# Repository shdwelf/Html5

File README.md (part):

# bip39-haiku-workbench

Offline workbench for mining **BIP-39 mnemonics that scan as 5-7-5 haiku**, deriving
their BIP-44 addresses, and moving data between tools through a **piped inbox**.

The application now combines both repository lineages. The canonical main canvas is
the complete uploaded **23 August Gen2 Webxdc/quine build**, with a surgical Poetry
validator repair applied before it executes rather than replacement look-alike
components. The small `⌘` switcher opens the maintained TypeScript recovery suite
and every other distinct, non-empty HTML application from the gen-2 patch.

```bash
npm install
npm run dev     # http://localhost:5173
npm test        # full test suite, including byte-identity locks for the uploads
npm run build   # dist/index.html + dist/bip39-haiku-workbench.xdc
```

The production build is inlined by `vite-plugin-singlefile`, so `dist/index.html`
runs standalone from the filesystem. `scripts/build-xdc.mjs` then packages that
same combined application, its icon, manifest, and static companion tools as a
Webxdc ZIP for ArcaneChat / Delta Chat.

## Combined codebases

| Switcher entry | Source | Integration rule |
| --- | --- | --- |
| **Gen2 · Aug 23** (default) | `bip39-haiku-workbench-gen2-2026-08-23T11-46-10-756Z.html` | Full uploaded 12-tool canvas plus strict Poetry syllable repair |
| **Gen2 · Aug 14** | `bip39-haiku-workbench-gen2-2026-08-14T20-01-22-058Z.html` | Exact earlier seven-tool generation |
| **Quip build** | `bip39-haiku-workbench-quip.html` | Exact mnemonic explorer bundle |
| **Classic wallet** | `bip39_haiku_wallet.html` | Exact standalone miner and encrypted wallet list |
| **Pattern validator** | `haikubip39.html` | Exact classic haiku/repeated-word validator |
| **Recovery suite** | `src/` | Maintained React/TypeScript tools described below |

The applications run in same-origin `iframe srcdoc` boundaries because every upload
is already a complete compiled document with its own React runtime, global CSS,
`#root`, storage, and download handlers. This is deliberate isolation, not a visual
port: `test/codebase-archive.test.tsx` pins the original SHA-256 of all five documents,
and `test/poetry-validation.test.ts` signature-locks the two targeted Gen2 repairs.
The old Poetry counter double-subtracted consonant-`le` endings, while its line builder
could abandon a target after drawing a word that did not fit. The repair shares the
validator pronunciation table, only selects words that fit the remainder, and accepts
exact form counts—never a third line of 4 or 6 for 5-7-5. The second 23 August upload
is omitted only because it has the same SHA-256 as the first; `bip39haiku.html` is
omitted because it is zero bytes.

## Provenance

This repository was empty apart from a README. The application source was recovered
from the archive repo [`shdwelf/Html5-sync-incoming`](https://github.com/shdwelf/Html5-sync-incoming):

| Piece | Recovered from |
| --- | --- |
| Workbench app (React + Vite + Tailwind, `src/lib/wallet.ts`, `src/lib/syllables.ts`, `src/lib/enso.ts`) | `build-bip-39-haiku-wallet.zip` |
| Piped inbox concept and UI | `hyper-portal-2.27.0-PIPED-installer.html` (inside `Internal storage.7z`) |
| Recovery Lab (missing-word brute force, typo/anagram repair, vanity mining) | `crypto-mnemonic-mining-app.zip` |
| Art Gallery catalog, greedy 5-7-5 fallback, syllable-exception cleanup | vanilla workbench in [`shdwelf/Html5`](https://github.com/shdwelf/Html5) (`js/haiku-catalog.js`, `js/syllables.js`) |
| Vault file format + standalone decryptor | `HAIKUv4/v5`/`DECRYPTORv1.html` lineage (`Haiku Supplies.zip`) and the vanilla workbench's WebCrypto vault |

The two never shipped together: the haiku workbench had no inbox, and the
hyper-portal build that had the inbox had no haiku tool. Wiring them together —
and repairing the inbox on the way — is what this repo does.

`scripts/wormhole-fetch.mjs` is a small utility kept from that recovery work:
given `WH_URL=<link>` it opens a wormhole.app drop in real chromium (via
playwright) and captures every file — the link is end-to-end encrypted in the
URL fragment, so only a real browser can decrypt it. It runs anywhere
playwright + chromium are installed (a laptop, a GitHub runner with the
workflow permission).

## Repository-wide Java / TiddlyWiki editions

The new [Repository Wiki build](tools/wiki-workspace/README.md) produces actual
ACME/TJWS-hosted `wiki.in.a.jar`, `more.wiki.in.a.jar`, and `tiddlywiki.in.a.jar`,
plus a native TiddlyWiki HTML/Webxdc edition and MediaWiki XML export. Each JAR
contains a per-file source catalog and a deduplicated exact-byte repository vault,
with private caches/credential paths explicitly excluded. The extended library
adds backlinks, bibliographic URLs, revision conflicts/history and Haiku-v1
compatible encrypted page/file exchange. These are **new repository editions**,
not a claim to have recovered historical More Wiki 0.9.9 or translated arbitrary
JavaScript into JavaCard. See the [source-checked research and limitations](docs/wiki-workspace-research-2026-10-15.md).

```sh
npm ci
npm run build:wiki-workspace           # JDK 11+, Python 3, tar, curl; outputs dist/wiki/
java -jar dist/wiki/more.wiki.in.a.jar 3003
npm run test:wiki-workspace
npm run test:wiki-server               # real executable-JAR HTTP + persistence tests
```

The classic wiki's Calendar now uses font-independent SVG navigation, an
always-visible month grid and an event-page form; no pre-existing events are
required. TiddlyWiki HTML/XDC carry previews and metadata; the complete eligible
binary vault lives in the JAR editions. Nothing is uploaded to a remote wiki.

## Standalone viewers

- **[HTML5 Offline Viewer](offline-viewer.html)** — curated public catalogue for the locally bundled Helios Observatory and Prime Viewer apps, plus the local WebXDC player. `python3 scripts/build-private-html5-offline-viewer.py` creates a separate ignored delivery ZIP from the same fixed app allowlist.
- **[HTML5 Offline Library for Android](apps/html5-offline-launcher/README.md)** — public and curated private APK build instructions. CI publishes only the public APK artifact; the two-app private APK is built and verified without public artifact upload.
- **[Wiki in a Jar](wikiinajar.html)** — the 2008 USB-stick personal wiki (`wiki.in.a.jar` 0.8) rebuilt as one offline HTML file and a Webxdc bundle: same `.wiki` page model, same `[[wiki:]]`/`[[img:]]`/`[[djvu:]]`/`[[tags:]]` namespaces, vCard contacts, DjVu reading via the vendored WASM decoder, and webxdc chat sync. Ships as `wikiinajar.xdc` (`npm run build:wikiinajar`) with the repository Markdown library (root deep dives + `docs/*.md`) converted to wiki pages in its Docs tab; see [the deep dive](wikiinajar-deep-dive.md), the seeded **Wiki in a Jar** documentation page inside the app, and the Java-side patch in [tools/wikiinajar/](tools/wikiinajar/).
- **[Keyspace Viewer](keyspace.html)** — BIP-39 geometry, measured statistical layers, wallet derivatives, and keyspace projections.
- **[Prime Viewer](prime.html)** — exact prime atlas, residue-class solar system, prime constellations, counting statistics, gaps, and integer inspection. See [PRIME.md](PRIME.md).
- **[Helios Observatory](astronomy.html)** — time-propagated solar orrery, curated celestial catalog, Earth-centered NEO radar, and modeled meteor streams. See [ASTRONOMY.md](ASTRONOMY.md).
- **[Flash Decompiler Timeline](flash-decompiler.html)** — Wayback/NATA2-style raw SWF retrieval, configurable CORS proxy triage, Behind The Dune version timeline, easter-egg notes, and a GitHub Actions path for JPEXS/FFDec decompilation without committing large NSFW binaries.
- **[Red October · 4D Command Theater](public/apps/red-october-command-viewer/)** — an offline story-index globe, selectable schematic silhouettes, story/time controls, VRML 2.0 and Xena XML export. The map markers are fictionalized narrative anchors, not real track data; the hull model has no precise internal layout. Ships as `red-october-command-viewer.xdc`; see [the viewer source/provenance research](docs/red-october-4dwm-research-2026-10-09.md) and [the Archive.org/Jane’s/Bulletin source audit](apps/red-october-command-viewer/data-sources/archive-research.md).
- **[Greeran Family Tree · 4DWM](greeran-family-4dwm.html)** — the Drive family-tree Webxdc with an offline spinning globe, playable 1774–2023 record timeline, Tree-of-Life preface, baseline GEDCOM export, and public-domain World English Bible EPUB. The first-name merge remains pending until an authorized Kirkpatrick ARJ and raw GEDCOM are available. See [the import/build notes](docs/greeran-family-4dwm.md) and [the ebook/data status](docs/greeran-family-tree-ebook-and-data-status.md).
- **[FOUR CORNERS 4Dwm](four-corners.html)** — the only place four US states meet: the surveyed quadripoint, Navajo volcanic field necks, the San Juan energy basin, the uranium legacy, and the ancestral Puebloan core, over a curated IDW relief that is honest about not being a DEM. See [docs/four-corners.md](docs/four-corners.md). Ships as `four-corners.xdc` and as the [TI calculator port](#four-corners-on-ti-calculators-four-corners-calc) below.
- **[SoCal Subsurface 4Dwm](socal-subsurface.html)** — an offline basin theater with terrain, geocache GPX import, radio/propagation and orbital views. Ships as `socal-subsurface.xdc`, plus the single-file [`socal-subsurface-inlined.html`](socal-subsurface-inlined.html) / `socal-subsurface-inlined.xdc` edition; the legacy download name `planet-viewer-4dwm.xdc` now carries this same canonical SoCal package and manifest.
- **[Greeran Subsurface 4Dwm](greeran-subsurface.html)** — the Greeran book's 2001 biography deep-dive (Glendora → West Covina → Goleta → Santa Barbara) rendered as a SOCAL-style subsurface theater. Ships as `greeran-subsurface.xdc`.
- **[Glendora High 4Dwm](glendora-high-4dwm.html)** — Class of 2001 at 1600 E Foothill Blvd, "now that I am a graduate". Ships as `glendora-high-4dwm.xdc`.
- **[ESGVROP 4Dwm](esgvrop-4dwm.html)** — East San Gabriel Valley ROP & Technical Center, the summer-2001 deep dive across the Del Norte and Sunflower campuses. Ships as `esgvrop-4dwm.xdc`.
- **[Dalton Race 4Dwm](dalton-race-4dwm.html)** — Big Dalton / Little Dalton terrain with pips, route pointers, and VRML export. Ships as `dalton-race-4dwm.xdc`.
- **[INGRESS INTEL 4Dwm](ingress-intel.html)** — an Ingress intel theater that actually tries to connect: a six-rung connection ladder (same-origin → your relay → public CORS proxy → pasted capture → webxdc peer → offline register) with a verdict and a fix printed per rung, the same intel payload drawn on a planet globe with geodesic links, spherical control fields and a live day/night terminator *and* on the SoCal basin plate, and an honest `SIM` watermark whenever nothing live answered. Decodes/encodes `getEntities`, portal-detail and plext payloads, IITC GeoJSON/KML/CSV exports and intel permalinks. Ships as `ingress-intel.xdc`. See [docs/ingress-intel-map-viewer.md](docs/ingress-intel-map-viewer.md) and the [connector research](docs/ingress-intel-connector-research-2026-10-07.md).
- **[CASEFILES · 4DWM](casefiles.html)** — the static-analysis lab for the 1998 kr0me corp Tripod library and the 1996 Rodger Ramrod DOS4GW package: Wayback CDX recovery behind a SHA-1 gate, fflate unzip in memory, SLEIGH x86 16/32, the Ghidra decompiler as WebAssembly — and a 4DWM plate that draws the capture corpus as a ridged relief over a playable capture-date timeline, and whatever artifact is on the table as a bit-plane relief with an offset sweep. Motif-style pips carry the record; VRML 2.0 exports the current field. Ships as `casefiles.xdc` (a real webxdc ZIP) and as the single-file `casefiles-inlined.html`; see [docs/casefiles-4dwm.md](docs/casefiles-4dwm.md).
- **[Lantronix Lab](lantronix-lab.html)** — the deep dive that starts at a thumb-sized Lantronix xPort Pro (16 MB flash, ColdFire, µClinux) and ends at a generated EAGLE design for a mains-powered RS-232 ↔ RJ45 wallplug: a device matrix that keeps DSTni-EX (x86) and DSTni-FX (ColdFire) apart, a client-side firmware triage tool that goes magic → container → architecture → Ghidra language, the µClinux stack Lantronix actually ships with a DistroWatch-reality-check on alternatives, a JVM-vs-Java-Card panel with a real `.class`/`.cap` reader and bytecode disassembler, and an EDA viewer that renders the generated `.sch`/`.brd` and re-runs the design rules in the browser. See [docs/lantronix-uclinux-deep-dive-2026-10-08.md](docs/lantronix-uclinux-deep-dive-2026-10-08.md) and [hardware/lantronix-wallplug/](hardware/lantronix-wallplug/).
- **Wallplug family** — the xPort Pro wallplug is now one of four generated, rule-checked EAGLE designs built by a single design-agnostic pipeline: a **WiMAX CPE** carrier for a PCI Express Mini Card 802.16e modem (Intel Centrino 6250; USB half wired, PCIe half honestly left open), a **Raspberry Pi Zero 2 W wall-socket** carrier with wired Ethernet (WIZnet WIZ850io on SPI0) and Ethernet-over-powerline (chargebyte PLC Stamp mini 2 on SPI1), and a standalone **HomePlug Green PHY ↔ Ethernet bridge** (QCA7005 + ESP32 + W5500). Every pad coordinate is imported from a published KiCad footprint by `tools/import-kicad-footprints.mjs`; creepage follows the chargebyte datasheet's 8 mm / 6.5 mm / 4000 Vac figures where that module is fitted; and `tools/replacement-parts.mjs` records 83 sourced substitutes with verdicts, including the ones marked *not-a-substitute*. See [docs/wimax-pi-powerline-variants-2026-10-08.md](docs/wimax-pi-powerline-variants-2026-10-08.md) and [hardware/](hardware/).
- **[CITY SUBSURFACE 4Dwm](lawrence-subsurface.html)** — the shared SoCal-family city engine ships as fifty-nine apps: Lawrence KS, Atlanta GA, Kansas City MO, Buffalo NY, Toronto ON, statewide California/Nevada/Arizona/Utah/Colorado/New Mexico/Oregon/Washington/Idaho/Montana/Wyoming/North Dakota/South Dakota/Nebraska/Kansas/Oklahoma/Texas/Iowa/Missouri/Minnesota/Louisiana/Mississippi/Alabama/Georgia/Wisconsin/Michigan/Illinois/Indiana/Ohio/Pennsylvania/Arkansas/Kentucky/Tennessee/Virginia/West Virginia/North Carolina/South Carolina/Florida/Maryland/Delaware/New Hampshire/Vermont/Maine/Massachusetts/Connecticut/Rhode Island/Alaska/New Jersey/New York/Hawaii frames, and Guam, American Samoa (Tutuila–Manuʻa), U.S. Virgin Islands and Midway territory frames. Each keeps the Gazetteer, local `rec.geocache` GPX import, BagIt export and plan view. Lawrence has a disclosed 8×8 USGS 3DEP sample grid plus five verified GNIS points; the state/territory starter registers use per-ID GNIS primary points with synthetic relief rather than claiming DEMs. Build with `npm run build:city-subsurface`; see [the evidence/build notes](docs/city-subsurface.md).
- **[COUNTRY VIEWER](country-viewer.html)** — the PC-Globe-style country viewer (S4 country thread): an offline, searchable full-coverage register of 233 countries/territories with CIA World Factbook notes, packaged as `country-viewer.xdc` — capital and reference-point coordinates, area, population, languages, government type, and national-anthem titles — pinned to `factbook/factbook.json@144d6977b2b0` with per-file SHA-256 in `resources/country-viewer/`. Build the dataset and bundle with `npm run build:country-viewer`. The 1990 PC Globe database itself is decoded by the dependency-free Java reader in `tools/pcglobe/` (dump in `research/pcglobe-java/`), and the [planet viewer](planet-viewer-4dwm.html) opens on a GLOBE plate that reuses the Red October globe with these capitals as markers.
- **[Historical Network Viewer — Keyhole slice](historical-network-viewer.html)** — the S6 evidence viewer for Denver's Keyhole BBS: dated observations, snapshot rights/capture status, a city-level place with no invented pin, merge/rejected-match logs, negative FidoNet searches, JSON/CSV export, and local TEXTFILES plus FTS-5000 FidoNet nodelist import with browser-side SHA-256. It is a citation fixture and local-import tool, not a bundled historical dataset; see [the fixture notes](docs/historical-network-keyhole-fixture-2026-10-22.md) and [FidoNet adapter notes](docs/historical-network-fidonet-adapter-2026-10-22.md).
- **[FOUR CORNERS · calculator port](four-corners-calc.html)** — the bench for the TI-83/89/92 port: it runs the port's own C core transpiled to an ES module, so the preview *is* the port.

Every 4Dwm-family Webxdc rebuilds from one command — `npm run build:4dwm`
chains the fourteen standalone packagers (casefiles, bluetops, cheyenne,
dalton-race, esgvrop, four-corners, glendora-high, greeran-family,
greeran-subsurface, ingress-intel, sanborn-restaurant, SoCal Subsurface (also
mirrored to the legacy `planet-viewer-4dwm.xdc` filename) and its inlined
edition, vincennes), then
builds the fifty-nine shared city/state/territory bundles; each app also has its own
`npm run build:<name>`, and `npm run check:casefiles` proves CASEFILES' two
derived artifacts still match their sources byte for byte.

## Tools

| Tab | Purpose |
| --- | --- |
| **Ensō Forge** | Parameterised ensō brushstroke; its packed *Ensō ID* doubles as the vault password. |
| **Haiku Wallet** | Mines 128-bit mnemonics until the 12 words partition into 5-7-5, derives `m/44'/0'/0'/0/0`, stores them in an AES-256 vault. |
| **Inspector** | Validates a phrase's BIP-39 checksum, shows its syllable/5-7-5 breakdown, derives address + xpub. |
| **Recovery Lab** | Brute-forces `?` words, repairs typos/anagrams, mines BTC vanity addresses — optionally pinned to an address fragment you know is yours. |
| **Art Gallery** | 100 curated checksum-valid BIP-39 art patterns (repeat stems, haiku/poetic scans), re-verified live on every render. |
| **MonKey Miner** | Mines Banano wallets for rare monKey accessories, fully offline. |
| **Autobiography** | Chapters plus an embedded filesystem; exports as one self-contained HTML book. |
| **Crypto Cookbook** | The 83-section reference, framed byte-identical from `/apps/cookbook/`. |
| **[OpenPGP Workbench](apps/openpgp-workbench/README.md)** | Local messages, public keyrings with fuzzy name/email search, and bounded private-key wordlist recovery. Fingerprint confirmations remain exact; filtering never reduces the full-ring export. |
| **Waves practice** | Explicitly synthetic paper portfolio/orders; no wallet, real funds, storage or exchange connection. [Scope and historical `.hts` investigation](docs/waves-paper-practice-2026-11-17.md). |
| Terminal / Market Data | Original tools; market prices are an offline simulation from the labeled historical snapshot, not live quotes. |

## Recovery Lab

Ported from the recovered `crypto-mnemonic-mining-app` (June 2026, ethers-based)
onto this repo's own stack — `@scure/bip39` for checksums, the wallet's BTC
P2PKH derivation instead of ethers/bananojs, no new heavy dependencies.

**Find `?` words.** Mark each unread word with `?`. A BIP-39 phrase carries its
own checksum, so of the 2048 words that could fill a slot only ~1 in 16
survives for a 12-word phrase (1 in 256 for 24 words) — the checksum does most
of the work. One missing slot scans instantly; two walks 2048² = 4.2M
combinations chunked and cancellably (a few minutes at most; more than two is
out of scope for a browser lab).

**Repair typos & anagrams.** Words outside the wordlist are replaced by their
anagrams (the wordlist has 56 anagram classes: `canoe/ocean`, `armed/dream`,
`alert/alter/later`…) and near edits — Levenshtein distance ≤ 2. If every word
is valid but the checksum still fails, each single word is tried against its
edit-distance-≤ 1 neighbours plus anagram mates, catching the silent swap that
spell-check cannot see.

**Pinning to an address.** Repairs and fills frequently have *several*
checksum-valid outcomes — the checksum cannot tell them apart. Paste the first
characters of an address you know the wallet owned and only candidates whose
BTC legacy derivation contains that fragment survive. That is also what makes
recovery deterministic instead of "first 20 valid hits".

**Vanity mining.** Mines fresh 12-word mnemonics until the BTC legacy address
starts with your prefix (case-sensitive Base58; the leading `1` is optional).
Each extra character is ~58× the work: two characters are seconds, three are
minutes, four are a long night. Cancels like everything else.

## Art Gallery

The 100-entry catalog shipped with the vanilla workbench port
(`js/haiku-catalog.js` in `shdwelf/Html5`): 40 eleven-word repeat stems with
their checksum word, 20 fifteen-word, 10 twenty-four-word patterns, and 30
haiku/poetic scans. In BIP-39 the last word is never free — its low bits are
the checksum of everything before it — so an eleven-word stem of one repeated
word pins exactly one valid ending. The stem is chosen; the checksum decides
the last word. These are found art.

Every card re-validates its phrase against the real BIP-39 checksum on render
(and `test/catalog.test.ts` locks all 100), so a corrupted import is visible
immediately. Haiku entries display their greedy 5-7-5 layout with per-line
syllable counts, and any entry can be piped to the Inspector.

## Inspector upgrades

- **Per-word chips** under the input — each word with its syllable count,
  red when not in the wordlist (ported from the mining app's live validation).
- **Explorer section** (Coleman-style): BIP-39 passphrase ("25th word"),
  custom derivation path, seed hex, root xpub, and a first-N accounts table.
  Private keys stay hidden behind a per-row reveal; the root xprv is never
  rendered. A passphrase changing every derived address is demonstrated in
  `test/syllables-explorer.test.ts`.
- **Greedy 5-7-5 fallback** now lives in `src/lib/syllables.ts`
  (`greedy575`), shared by the Inspector and by `itemFromMnemonic`, replacing
  the old behaviour of dumping a non-haiku phrase onto a single line. The
  ported version had a defect: words after the third line filled were
  silently dropped. Fixed here — the layout always accounts for every word —
  and locked by test.
- The syllable **exception table** dropped three dead keys (`area51`,
  `create_`, `science_`) that could never match after non-letters are
  stripped.

## Vault files and the standalone decryptor

Besides the existing crypto-js exports, the wallet now speaks a
format-designed-for-archival vault file:

```
haiku-vault-v1.<base64( 0x01 | salt(16) | iv(12) | ciphertext‖tag )>
```

AES-256-GCM, PBKDF2-HMAC-SHA256 × 120,000, salt separate from the IV so one
Ensō ID can safely back multiple files. Implemented with `@noble/ciphers` in
the app; round-trip, wrong-password and single-character-tamper cases are
covered by `test/vaultfile.test.ts`.

**🧰 Standalone decryptor ⬇** generates a single self-contained HTML page
(no imports, no network, verified by test) that decrypts `.haikuvault` files
with native WebCrypto — optionally with the current vault pre-embedded. Save
it next to your backups: it opens from a USB stick in fifty years' time, which
is the whole point of an offline vault. **📥 Import .haikuvault** decrypts
with the current Ensō ID and merges without duplicates.

## The piped inbox

Any tool can **park** a value in the inbox (`📤 Pipe`) or **pull** one out
(`📥 Pull from Pipe`). The floating inbox can also **push** a value straight into
a tool, which focuses that tab and delivers the payload.

Content is typed (`mnemonic`, `haiku`, `address`, `xpub`, `json`, `text`) and the
UI only offers targets that accept the type — so a mnemonic mined in the wallet
can be sent to the Inspector, but an address cannot.

### What was broken

The original provider (`hyper-portal-2.27.0-PIPED-installer.html`) kept a single
`inboundPayload` slot and no persistence. Four concrete defects, each now covered
by a regression test in `src/pipe/PipeProvider.test.tsx`:

1. **Back-to-back sends lost data.** Delivery was one `useState` slot, so
   `sendToTool(a); sendToTool(b)` overwrote `a` before any consumer ran — only
   `b` arrived. Deliveries are now an append-only queue drained per tool.

2. **The inbox did not survive a reload.** Pipes lived only in React state, which
   makes "park this for later" meaningless across a refresh. Pipes and in-flight
   deliveries now persist to `localStorage`, with corrupt/quota-limited storage
   degrading to memory instead of throwing.

3. **Empty content read back as a miss.** `consumePipe` ended in
   `?.content || null`, so an empty string — legitimate payload — was
   indistinguishable from a missing pipe. Now `?? null`.

4. **Colliding ids.** Ids came from `Math.random().toString(36).substring(2,10)`.
   Since rows are keyed by id and `removePipe` filters on it, a collision deletes
   the wrong entry. Now `crypto.randomUUID()` with a timestamped fallback.

Additionally, consumption used to be an impure read (`consumeInbound` returned the
payload *and* cleared it), which is fragile under React StrictMode's double-invoked
effects. Delivery is now explicit: `usePipeReceiver` hands the payload to a handler,
records the delivery id in a ref, and acks it — so a repeated effect run cannot
apply the same payload twice.

I verified 1, 3 and 4 by running the new tests against a faithful replica of the
original provider and watching them fail. Defect 2 is likewise reproduced. The
late-mount guarantee (a delivery waits for a tool that has not been opened yet) is
hardening rather than a reproduced regression — the old code happened to survive
that case.

### Using it in a tool

```tsx
// produce
<PipeOutButton draft={{
  content: item.mnemonic, contentType: "mnemonic",
  sourceId: "wallet", sourceName: "Haiku Wallet", label: `${item.id} mnemonic`,
}} />

// consume: pushed deliveries
usePipeReceiver("inspector", (delivery) => setText(delivery.content));

// consume: user-initiated pull
<PipeInButton accepts={["mnemonic", "text"]} onReceive={(content) => setText(content)} />
```

## Recovered HTML5 apps (`/apps/`)

`npm run dev` also serves the other apps recovered from `Html5-sync-incoming`,
over the dev server's origin rather than `file://`:

| URL | App |
| --- | --- |
| `/apps/` | Index, with a live secure-context / microphone check |
| `/apps/anc-studio/` | ANC Studio Ultra — adaptive multi-band FxLMS over AudioWorklet |
| `/apps/sound-sanctuary/` | Sound Sanctuary — complete local Noise Canceling Sanctuary snapshot; microphone opt-in, not hearing protection |
| `/apps/aura-sound-studio/` | AURA Sound Studio — complete local DSP lab, with its alternate saved-settings snapshot; not certified branded processing |
| `/apps/armstrong-madison/` | Armstrong–Madison Cipher Lab — supplied 18-section workbench plus offline source review, literal AFIO-key audit and explicit-only working-key save/share; no verified complete decipherment. [Research and build notes](docs/armstrong-madison-cipher-review-2026-11-17.md). |
| `/apps/torrent-atlas/` | Torrent Atlas — local magnet/torrent inspection and v1 creation, explicit outbound search links and qualified password-manager research; no swarm activity |
| `/apps/openpgp-workbench/` | Local OpenPGP tools, verified Android file saves and opt-in PUBLIC certificate remembering; no automatic secret storage |
| `/apps/cyberchef/` | CyberChef Renovated Kitchen — 519 recipes after unioning the Html5 and Html5-sync-incoming recipe sets, plus file input and save. Includes QR/Aztec generation and image decoding, CueCat and postal barcode recipes, Avery LabelPro-style N-up labels, an educational multiplicative ElGamal demonstration (not FHE), and offline SFX support. See the [barcode notes](docs/cyberchef-aztec-cuecat.md), [SFX coverage audit](docs/cyberchef-sfx-coverage-audit-2026-10-13.md), [field-cipher deep dive](docs/field-cipher-deep-dive-2026-10-14.md), and [recipe-sourcing notes](docs/recipe-sourcing-round-4-2026-10-14.md) and [round 5](docs/recipe-sourcing-round-5-2026-10-14.md) for the tested cryptography and historical recipes. |
| `/apps/red-october-command-viewer/` | Offline fictionalized story-index globe and schematic profile viewer; exports VRML 2.0 and a Xena binary-preservation XML wrapper. No real submarine tracks or precise internal layouts. Ships as `red-october-command-viewer.xdc`. |
| `/apps/cookbook/` | Crypto Cookbook — 83-section reference, framed by the Cookbook tab |
| `/apps/cryptofountain-bbs/` | CryptoFountain BBS — P2P microblogging with erasure codes |

The complete browser catalog is generated with `npm run build:app-catalog` and
contains the same 98 reviewed public entrypoints as the Android catalog, not
only the highlights above. `npm run audit:app-sources` separately accounts for
all tracked imported and maintained source entrypoints without auto-publishing private research,
wallet candidates or unbuilt shells. See the [Android save and data-retention
notes](apps/html5-offline-launcher/README.md) before upgrading/reinstalling.

The BBS shipped with a Cloudflare Insights beacon; it has been stripped so the
page is fully self-contained and makes no external requests.

### Why serving them matters

`getUserMedia` is only available in a [secure context](https://developer.mozilla.org/docs/Web/Security/Secure_Contexts).
Local-file handling varies by browser and is not a reliable deployment path.
Serve from HTTPS or an HTTP loopback development origin; microphone capture
still requires your consent and appropriate OS permissions. This is not a
claim of certified acoustic ANC or hearing protection.
The same applies to the MonKey API: `file://` pages get a `null` origin, which
CORS rejects.

A small Vite middleware (`appsDirectoryIndex` in `vite.config.ts`) rewrites
directory URLs under `/apps/` to their `index.html`, which the SPA fallback
would otherwise swallow.

### CyberChef: file input, byte-exact Base64, save

The kitchen had no file input and no way to save output, and its `To Base64`
operation was `b64FromBytes(utf8Encode(text))` — running bytes through UTF-8,
which corrupts anything that isn't valid UTF-8. Added:

- **📁 Load File** — reads raw bytes. The loaded file (not the textarea)
  becomes the pipeline source, so binary is never re-encoded.
- **File / Binary to Base64** — byte-exact, with optional line wrapping.
  Also **Base64 to File / Binary** and **File / Binary to Data URI**.
- **→ Base64** — one-click recipe: prompts for a file and encodes it.
- **💾 Save Output** — downloads the result. Base64 output is decoded back to
  real bytes, so *File → Base64 → Save* reproduces the original file.

### CyberChef: Base62 and encrypt-to-link

- **To Base62 / From Base62** — radix 256→62 over the `0-9 A-Z a-z` alphabet.
  URL-safe with no padding and nothing to percent-escape, byte-exact, and
  leading zero bytes are preserved as leading `0` characters like Base58.
- **AES-GCM File (password)** — the existing `AES-GCM` op runs data through
  `TextEncoder`, so it corrupts any non-UTF-8 file. This one operates on raw
  bytes. Layout is `salt(16) ‖ iv(12) ‖ ciphertext ‖ tag`, PBKDF2-SHA256 at
  250k iterations, with the salt separate from the IV so one password can be
  reused across messages.
- **Encrypt to Link / Decrypt from Link** — packs the ciphertext into a URL
  fragment (`#k=…`). The fragment is never sent to the server hosting the page.

Verified in Node against a 2,000-byte binary with leading zeros: exact
round-trip, wrong password rejected, single-character tampering caught by the
GCM tag, and a fresh salt+IV on every encryption.

**Size ceiling, and it is low.** Base62 expands data ~1.34×, and AES-GCM adds 44
bytes of header and tag. A 2 KB file becomes a **2,781-character URL** — already
past the ~2,000 characters most servers and shorteners accept. Worse, link
shorteners routinely drop everything after `#`, which is exactly where the
ciphertext lives. `Encrypt to Link` warns when the URL crosses 2,000 characters.
For anything but a short note, encrypt to a *file* and share a link to the file.

Binary travels the text pipeline as a Latin-1 string (one code unit per byte)
via `binStrFromBytes` / `bytesFromBinStr`. Verified on a 4096-byte adversarial
payload including NULs and `0xFF`: the output equals Node's
`Buffer.toString("base64")` exactly, while the old UTF-8 path does not.

## Ghidra + CyberChef safe-source workflows

The in-app recipe packs cover byte-safe encoding, toy XOR/crib work,
round-trip cipher demonstrations, and static MZ-header preflight. They reuse
existing CyberChef operations; they do not emulate or launch programs. The
source assessment for `N17Pro3426/ViewerMade` records why that compiled malware
zoo was **not cloned or imported**. See
[`docs/ghidra-cyberchef-recipes.md`](docs/ghidra-cyberchef-recipes.md),
[`docs/ghidra-headless-benign-sample-methodology.md`](docs/ghidra-headless-benign-sample-methodology.md),
and [`docs/geomate-viewermade-source-check-2026-10-07.md`](docs/geomate-viewermade-source-check-2026-10-07.md).
Geomate.jr analysis is separately gated by the reverse-engineering clause in
the Brand 44 User's Guide; no Geomate.jr binary analysis is claimed.

## MonKey Miner

The `🐒 MonKey Miner` tab generates real Banano wallets (`bananocurrency-web`)
and keeps the ones whose monKey wears the accessories you're hunting.

The original build called `monkey.banano.cc/api/v1/monkey/dtl/<address>` for every
candidate, so it needed the network, was rate-limited, and produced no cards at
all offline. Accessories are now derived **locally from the address**, the same
way the real service derives them deterministically.

### Odds are the real ones

Verified against [appditto/MonKey](https://github.com/appditto/MonKey), whose
**code** is MIT:

| Source | What it gives |
| --- | --- |
| `server/image/accessories.go` | category chances — glasses .25, hat .35, misc .3, shirt/pants .25, shoes .22, tail .2, mouth always |
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
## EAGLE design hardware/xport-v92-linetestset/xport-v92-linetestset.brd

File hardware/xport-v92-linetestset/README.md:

# Isolated Line Test Set — `xport-v92-linetestset`

A lineman's test handset on a board. Test leads on one side, an earpiece and an
electret microphone on the other, with a 600:600 Ω wet isolation transformer in
between and a switch that chooses whether you are *part of* the call or merely
listening to it.

This is the legitimate member of the phreaking "box" family — the **beige box**,
which is not a fraud device at all but a standard telecom maintenance tool that
Fluke and Greenlee sell commercially. Clipping it onto a line that is not yours
is wiretapping and is illegal; the hardware is not. See
[`docs/phreaking-boxes-vlsi-notes.md`](../../docs/phreaking-boxes-vlsi-notes.md)
for the rest of that family and why this one is different.

Generated from
[`tools/xport-v92-linetestset-model.mjs`](../../tools/xport-v92-linetestset-model.mjs)
and verified by that tool's `--check`:

```
geometry: 69 pads, 33 placed elements, 27 nets
worst mains↔SELV creepage: 3.28 mm (T1.1 ↔ T1.6), limit 3 mm
schematic: 29 instances on a 520 × 420 mm sheet
OK — XML well-formed, every reference resolves, connectivity matches the model, geometry clean.
```

## Signal chain

```
test leads
  └─ F1 100mA ─ R1/R2 100R ─┬─ RV1 275V ─┬─ C1 100nF ─┐
                            └────────────┴────────────┴─ BR1 bridge rectifier
                                                            └─ K1 hook relay
                                                                 └─ T1 wet 600:600
                                                                      └─ hybrid
                                                                          ├─ TALK 600R ──► earpiece + electret
                                                                          └─ MON  10k ──► volume ──► earpiece
```

## The three things that make it a test set and not an audio tap

**1. The bridge rectifier.** A test set gets clipped onto pairs whose polarity
nobody knows. Full-wave rectifying ahead of everything else means the rest of
the circuit always sees the same orientation. Without `BR1`, half of every job
is guessing which lead is tip.

**2. TALK versus MONITOR are opposite requirements.** TALK goes off-hook and
terminates the line in 600 Ω so you can join the conversation. MONITOR bridges
at 10 kΩ, which is high enough not to load the line or disturb a call already in
progress, so you can listen and measure without anyone knowing. `SW1` selects
between them; there is no setting that does both.

**3. It runs from the line.** The electret bias (`R7` 2.2 k) and the line-present
LED (`R8` 1 k) are fed from the rectified loop. No battery to be flat when you
are standing at a cabinet in the rain, and the LED glows on ring voltage too, so
it doubles as an EMF indicator.

## DC loop budget in TALK

This decides whether the exchange sees an off-hook at all.

| element | resistance |
| --- | --- |
| F1 fuse | ~0.2 Ω |
| R1 + R2 surge limiters | 200 Ω |
| BR1 bridge | a few Ω effective |
| K1 contact | ~0.1 Ω |
| T1 primary DC resistance | 40–150 Ω |
| **total** | **240–350 Ω** (limit 400 Ω) |

## Safety

The left of the board is line-referenced. 48 V DC sits on the pair, ring peaks
above 150 V, and a lightning or power-cross event puts far more on it.

`T1` is the **only** isolation barrier between the line and the earpiece you put
against your head. It must be the **wet** type — specified to carry 20–50 mA of
DC loop current without saturating. A dry voice transformer of the same
impedance works on the bench and fails the moment the line goes off-hook.

Isolation resistance from the line side to any touchable metal has to hold
**5 MΩ measured at 100 V DC**. Measure it after assembly, before first use.

The 3 mm creepage is enforced by `tools/wallplug-drc.mjs` via
`BOARD.zones.mains` and `creepageMm: 3.0`, and `T1`'s primary pins are marked
line-referenced individually through `PARTS[].padZones`, so the checker measures
the transformer's own pin spacing rather than trusting its silk outline. As
built, the worst pair is **T1.1 ↔ T1.6 at 3.28 mm**.

## Files

| file | what |
| --- | --- |
| `xport-v92-linetestset.lbr` | 18 packages, 18 symbols, 19 devicesets |
| `xport-v92-linetestset.sch` | 29 instances on a 520 × 420 sheet |
| `xport-v92-linetestset.brd` | 69 pads, 33 elements, 27 nets, 110 × 80 mm |
| `BOM.md` | generated bill of materials |

Rebuild with `npm run build:xport-v92-linetestset`, or check without writing:
`node tools/build-wallplug-eagle.mjs --check --design xport-v92-linetestset`.

Fourteen of the packages are shared with
[`../xport-v92-audiobridge/`](../xport-v92-audiobridge/) by direct import rather
than by copy, so the two boards cannot drift apart on a footprint. Only the
bridge rectifier, SPDT toggle, earpiece and electret are new.

## What is not done

- **No routing.** The emitter places parts and verifies clearance; it does not
  route copper. `POUR` and the barrier keep-out are declared, traces are not.
- **Not measured.** No prototype. Return loss against the 10 dB requirement,
  frequency response, sidetone null and THD are all unmeasured, and the hybrid
  balance in particular has to be trimmed against a real line.
- **No sidetone or ringer.** A production butt set has both. This has an
  earpiece, a microphone and a volume control, and nothing else.
- **`LS1` and `MIC1` values are placeholders.** A 150 Ω earpiece and a generic
  electret are assumed; the bias resistor `R7`/`R10` divider was sized for a
  typical 2 V, 0.5 mA capsule, not for a specific part.
- **Hook drive is external.** `J2` expects a control signal; the set does not
  decide for itself when to go off-hook.

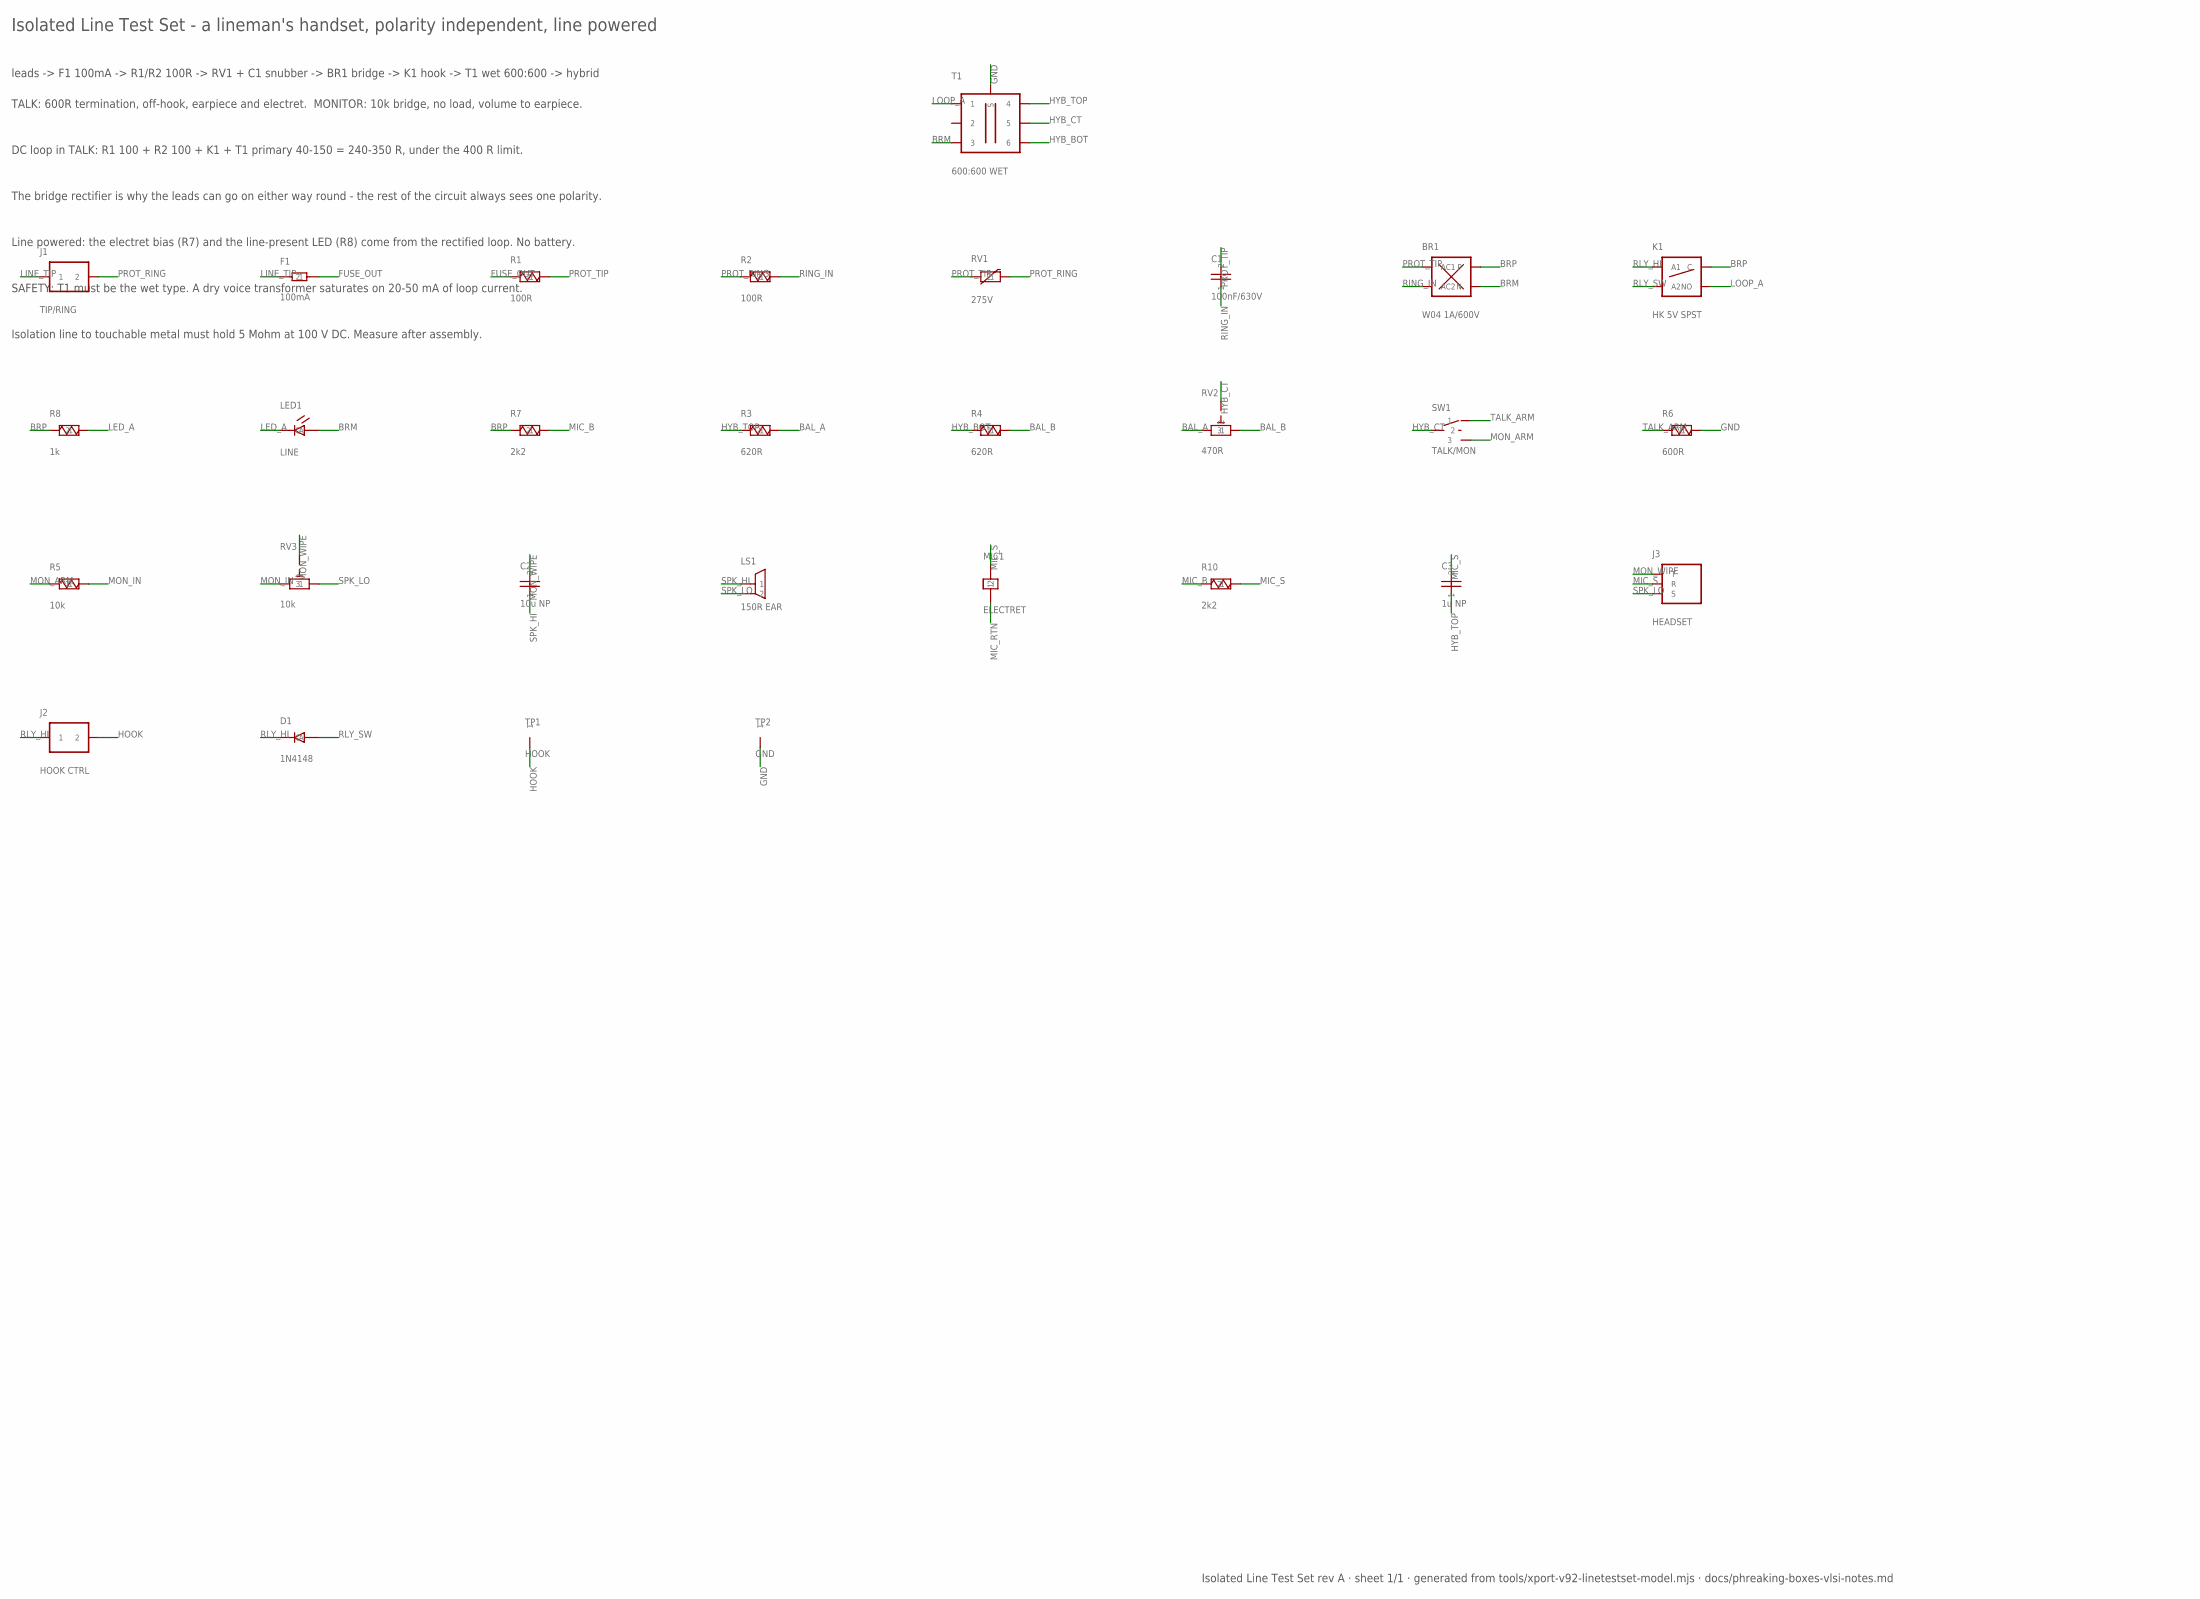
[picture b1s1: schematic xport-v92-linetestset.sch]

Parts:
BR1: W04 1A/600V; BRIDGE-WOB
C1: 100nF/630V; C-5.08
C2: 10u NP; C-5.08
C3: 1u NP; C-5.08
D1: 1N4148; DO41
F1: 100mA; R-7.62
J1: TIP/RING; TERM2-5.08
J2: HOOK CTRL; TERM2-5.08
J3: HEADSET; JACK-3P5
K1: HK 5V SPST; RELAY-SPST
LED1: LINE; LED-5MM
LS1: 150R EAR; SPEAKER-12
MIC1: ELECTRET; ELECTRET-10
R1, R2: 100R; R-7.62
R3, R4: 620R; R-7.62
R5: 10k; R-7.62
R6: 600R; R-7.62
R7, R10: 2k2; R-7.62
R8: 1k; R-7.62
RV1: 275V; MOV-7.62
RV2: 470R; TRIM-3P
RV3: 10k; TRIM-3P
SW1: TALK/MON; TOGGLE-SPDT
T1: 600:600 WET; XFMR-600
TP1: HOOK; TP
TP2: GND; TP

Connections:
BAL_A: R3.2, RV2.1
BAL_B: R4.2, RV2.3
BRM: BR1.- (N), LED1.2 (C), T1.3
BRP: BR1.+, K1.3 (C), R7.1, R8.1
FUSE_OUT: F1.2, R1.1
GND: R6.2, T1.S, TP2.1
HOOK: J2.2, TP1.1
HYB_BOT: R4.1, T1.6
HYB_CT: RV2.2, SW1.2, T1.5
HYB_TOP: C3.2, R3.1, T1.4
LED_A: LED1.1 (A), R8.2
LINE_TIP: F1.1, J1.1
LOOP_A: K1.4 (NO), T1.1
MIC_B: R7.2, R10.1
MIC_RTN: MIC1.2
MIC_S: C3.1, J3.2 (R), MIC1.1, R10.2
MON_ARM: R5.1, SW1.3
MON_IN: R5.2, RV3.1
MON_WIPE: C2.1, J3.1 (T), RV3.2
PROT_RING: J1.2, R2.1, RV1.2
PROT_TIP: BR1.~1 (AC1), C1.1, R1.2, RV1.1
RING_IN: BR1.~2 (AC2), C1.2, R2.2
RLY_HI: D1.1 (A), J2.1, K1.1 (A1)
RLY_SW: D1.2 (C), K1.2 (A2)
SPK_HI: C2.2, LS1.1
SPK_LO: J3.3 (S), LS1.2, RV3.3
TALK_ARM: R6.1, SW1.1

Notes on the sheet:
Isolated Line Test Set - a lineman's handset, polarity independent, line powered
leads -> F1 100mA -> R1/R2 100R -> RV1 + C1 snubber -> BR1 bridge -> K1 hook -> T1 wet 600:600 -> hybrid
TALK: 600R termination, off-hook, earpiece and electret. MONITOR: 10k bridge, no load, volume to earpiece.
DC loop in TALK: R1 100 + R2 100 + K1 + T1 primary 40-150 = 240-350 R, under the 400 R limit.
The bridge rectifier is why the leads can go on either way round - the rest of the circuit always sees one polarity.
Line powered: the electret bias (R7) and the line-present LED (R8) come from the rectified loop. No battery.
SAFETY: T1 must be the wet type. A dry voice transformer saturates on 20-50 mA of loop current.
Isolation line to touchable metal must hold 5 Mohm at 100 V DC. Measure after assembly.
Isolated Line Test Set rev A · sheet 1/1 · generated from tools/xport-v92-linetestset-model.mjs · docs/phreaking-boxes-vlsi-notes.md

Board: 2 copper layers, 33 parts (0 on the bottom side), 26 nets, no tracks yet.

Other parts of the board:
H1, H2, H3, H4: MOUNT-M3

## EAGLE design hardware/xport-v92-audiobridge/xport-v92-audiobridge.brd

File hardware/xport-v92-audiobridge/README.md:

# POTS Audio Bridge — `xport-v92-audiobridge`

Telephone line on one side, a sound card microphone input and an agent headset on
the other. Second sheet of the xPort Pro V.92 card family; pairs with
[`../xport-v92-faxcard/`](../xport-v92-faxcard/), which does the fax and data
side of the same line.

Generated from [`tools/xport-v92-audiobridge-model.mjs`](../../tools/xport-v92-audiobridge-model.mjs)
by `tools/build-wallplug-eagle.mjs`, and verified by that tool's `--check`:
XML well-formed, every pin reference resolves, the emitted connectivity matches
the model's net table, and the geometry DRC passes.

## Signal chain

```
PSTN tip/ring
  └─ F1 50 mA ─ R1 100R ─┬─ RV1 275V ─┬─ C1 100nF ─┐   (surge + snubber)
                         └────────────┴────────────┴─ K1 hook relay
                                                        └─ T1 600:600 "wet"
                                                             ├─ centre-tapped hybrid
                                                             │    (620R x2 + RV2 470R trim)
                                                             ├─ 40 dB pad ──────────► J2 MIC IN
                                                             ├─ 15 dB pad ◄────────── J3 CARD OUT
                                                             └─ headset ────────────► J4 HEADSET
```

## Why each part is there

**The transformer has to be the "wet" type.** A wet 600:600 transformer is
specified to carry the 20–50 mA of DC loop current without saturating; a dry
voice transformer of the same impedance will work on the bench and go quiet or
distort the moment the line goes off-hook. Typical wet transformer DC resistance
is 40–150 Ω and inductance a few henries — that inductance is also what sets the
low-frequency response.

**The hybrid converts 2-wire to 4-wire.** The line is one pair; a sound card has
separate send and receive. Without the hybrid the agent hears their own voice a
beat late. This one is the resistive Wheatstone bridge of four 620 Ω arms, one
arm being the line itself in series with a DC blocking capacitor, nulled by the
470 Ω trimmer. The trimmer is not optional: a real line is not 600 Ω, and a
fixed resistor never nulls properly. Adjust for minimum sidetone with a real line
connected.

**The DC loop budget decides whether the exchange acknowledges the off-hook:**

| element | resistance |
| --- | --- |
| R1 surge limiter, tip | 100 Ω |
| R2 surge limiter, ring | 100 Ω |
| K1 relay contact | ~0.1 Ω |
| T1 primary DC resistance | 40–150 Ω |
| **total** | **240–350 Ω** (limit: 400 Ω) |

**The pads are sized from the actual levels**, not copied from a diagram:

- POTS nominal is −9 dBm, 275 mV rms into 600 Ω, 300–3400 Hz.
- A sound card line output is about 1 V rms; its microphone input is about 10 mV
  and supplies a ~5 V bias.
- Line → mic: R8 10 k series + R9 100 Ω shunt = **40 dB**, the conventional pad
  for this interface. R10 2.2 k keeps the card's bias current out of the
  transformer.
- Card → line: R13 470 Ω + R14 100 Ω = **15 dB**, deliberately heavier than the
  ~11 dB the levels need. Better to run the line slightly quiet than to
  overdrive the far end.

## Safety

The left of the board is line-referenced. 48 V DC sits on the pair, ring peaks
above 150 V, and a lightning or power-cross event puts far more on it.

T1 is the **only** isolation barrier between that and the PC. If you replace it
with anything not rated for the line, the sound card and the PC chassis become
part of the telephone circuit.

Isolation resistance from the line side to any touchable metal has to hold
**5 MΩ measured at 100 V DC**. Measure it after assembly.

The 3 mm creepage between the line side and the SELV side is enforced by
`tools/wallplug-drc.mjs` — `BOARD.zones.mains` and `creepageMm: 3.0` — and
T1's primary pins are individually marked line-referenced through
`PARTS[].padZones`, so the checker measures the transformer's own pin spacing
rather than trusting its silk outline. As built, the worst pair is
**T1.1 ↔ T1.6 at 3.28 mm**.

## Regulatory — read before connecting to a public network

**This is not a certified Direct Access Arrangement and is not approved for
connection to a public network.** Connecting terminal equipment to the PSTN is
regulated — FCC Part 68 in the United States, equivalent national approvals
elsewhere — and compliance is what a DAA is for: an approved module providing
the hook switch, the isolation and the impedance. Xecom, Cermetek and Siemens
all make them.

Two ways to stay legal:

1. **Put an approved DAA in front of this board.** Connect the hybrid behind the
   DAA rather than to the line directly.
2. **Keep this board on the private side of the network** — behind a PBX, or on
   a bench line — where no approval applies.

A third option worth considering: the V.92 module in the companion card already
has an approved DAA with 3 kV isolation, so take audio from *its* pins instead
of from the line. Whether the specific module exposes mic/speaker pins is not
something this repository has verified — check the datasheet before committing
to that route.

## Files

| file | what |
| --- | --- |
| `xport-v92-audiobridge.lbr` | 14 packages, 14 symbols, 15 devicesets |
| `xport-v92-audiobridge.sch` | 39 instances on a 520 × 420 sheet |
| `xport-v92-audiobridge.brd` | 88 pads, 43 elements, 29 nets, 120 × 90 mm |
| `BOM.md` | generated bill of materials |

Rebuild with `npm run build:xport-v92-audiobridge`, or check without writing
using `node tools/build-wallplug-eagle.mjs --check --design xport-v92-audiobridge`.

## What is not done

- **No layout routing.** The emitter places parts and verifies clearance; it
  does not route copper. `POUR` and the barrier are declared, traces are not.
- **Not measured.** No prototype, no return-loss measurement against the 10 dB
  requirement, no THD or frequency-response numbers. The hybrid balance in
  particular has to be trimmed against a real line.
- **Component values are computed, not validated.** The pad ratios follow from
  the published POTS and sound-card levels, but no scope trace confirms them.
- **The headset path is passive.** It will drive a headset from the hybrid; it
  will not drive a speaker. An agent needing hands-free volume wants an
  amplifier stage that is not on this board.

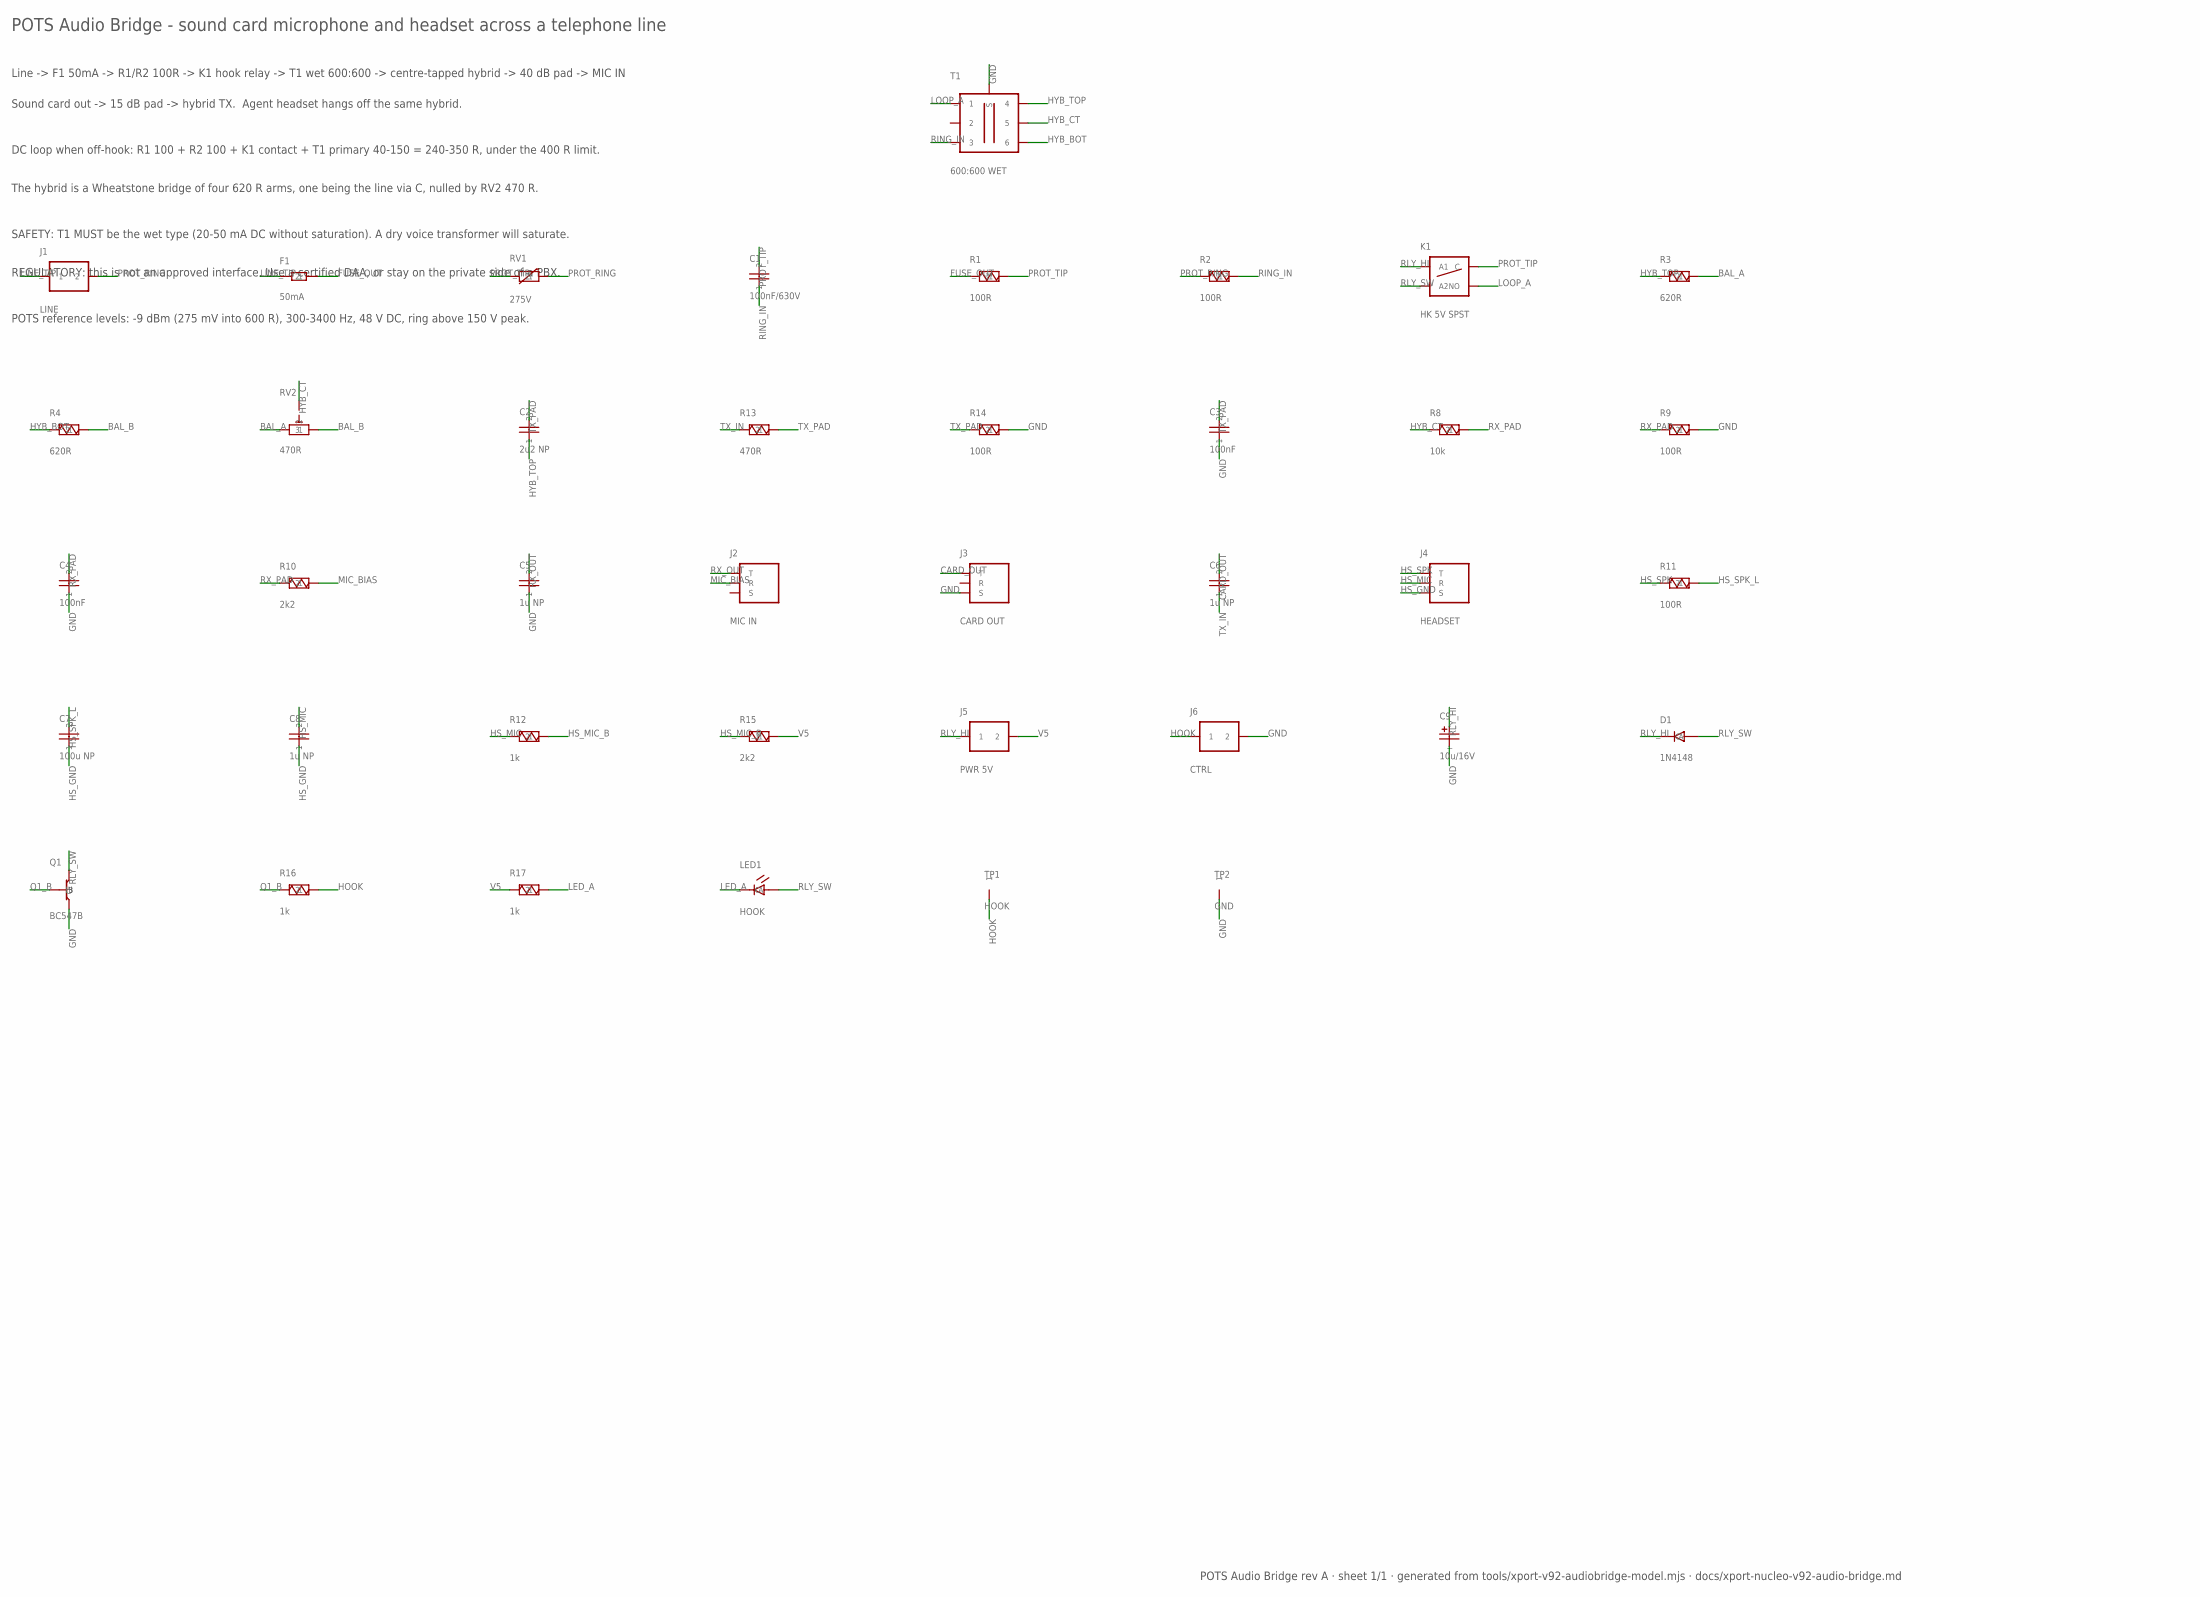
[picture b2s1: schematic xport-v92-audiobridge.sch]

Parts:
C1: 100nF/630V; C-5.08
C2: 2u2 NP; C-5.08
C3, C4: 100nF; C-5.08
C5, C6, C8: 1u NP; C-5.08
C7: 100u NP; C-5.08
C9: 10u/16V; CP-D8-P3.5
D1: 1N4148; DO41
F1: 50mA; R-7.62
J1: LINE; TERM2-5.08
J2: MIC IN; JACK-3P5
J3: CARD OUT; JACK-3P5
J4: HEADSET; JACK-3P5
J5: PWR 5V; TERM2-5.08
J6: CTRL; TERM2-5.08
K1: HK 5V SPST; RELAY-SPST
LED1: HOOK; LED-5MM
Q1: BC547B; TO92
R1, R2, R9, R11, R14: 100R; R-7.62
R3, R4: 620R; R-7.62
R8: 10k; R-7.62
R10, R15: 2k2; R-7.62
R12, R16, R17: 1k; R-7.62
R13: 470R; R-7.62
RV1: 275V; MOV-7.62
RV2: 470R; TRIM-3P
T1: 600:600 WET; XFMR-600
TP1: HOOK; TP
TP2: GND; TP

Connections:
BAL_A: R3.2, RV2.1
BAL_B: R4.2, RV2.3
CARD_OUT: C6.1, J3.1 (T)
FUSE_OUT: F1.2, R1.1
GND: C3.2, C4.2, C5.2, C9.2 (-), J3.3 (S), J6.2, Q1.3 (E), R9.2, R14.2, T1.S, TP2.1
HOOK: J6.1, R16.2, TP1.1
HS_GND: C7.2, C8.2, J4.3 (S)
HS_MIC: C8.1, J4.2 (R), R12.1
HS_MIC_B: R12.2, R15.1
HS_SPK: J4.1 (T), R11.1
HS_SPK_L: C7.1, R11.2
HYB_BOT: R4.1, T1.6
HYB_CT: R8.1, RV2.2, T1.5
HYB_TOP: C2.2, R3.1, T1.4
LED_A: LED1.1 (A), R17.2
LINE_TIP: F1.1, J1.1
LOOP_A: K1.4 (NO), T1.1
MIC_BIAS: J2.2 (R), R10.2
PROT_RING: J1.2, R2.1, RV1.2
PROT_TIP: C1.1, K1.3 (C), R1.2, RV1.1
Q1_B: Q1.1 (B), R16.1
RING_IN: C1.2, R2.2, T1.3
RLY_HI: C9.1 (+), D1.1 (A), J5.1, K1.1 (A1)
RLY_SW: D1.2 (C), K1.2 (A2), LED1.2 (C), Q1.2 (C)
RX_OUT: C5.1, J2.1 (T)
RX_PAD: C4.1, R8.2, R9.1, R10.1
TX_IN: C6.2, R13.1
TX_PAD: C2.1, C3.1, R13.2, R14.1
V5: J5.2, R15.2, R17.1

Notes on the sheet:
POTS Audio Bridge - sound card microphone and headset across a telephone line
Line -> F1 50mA -> R1/R2 100R -> K1 hook relay -> T1 wet 600:600 -> centre-tapped hybrid -> 40 dB pad -> MIC IN
Sound card out -> 15 dB pad -> hybrid TX. Agent headset hangs off the same hybrid.
DC loop when off-hook: R1 100 + R2 100 + K1 contact + T1 primary 40-150 = 240-350 R, under the 400 R limit.
The hybrid is a Wheatstone bridge of four 620 R arms, one being the line via C, nulled by RV2 470 R.
SAFETY: T1 MUST be the wet type (20-50 mA DC without saturation). A dry voice transformer will saturate.
REGULATORY: this is not an approved interface. Use a certified DAA, or stay on the private side of a PBX.
POTS reference levels: -9 dBm (275 mV into 600 R), 300-3400 Hz, 48 V DC, ring above 150 V peak.
POTS Audio Bridge rev A · sheet 1/1 · generated from tools/xport-v92-audiobridge-model.mjs · docs/xport-nucleo-v92-audio-bridge.md

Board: 2 copper layers, 43 parts (0 on the bottom side), 29 nets, no tracks yet.

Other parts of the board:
H1, H2, H3, H4: MOUNT-M3

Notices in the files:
README.md:
its licence: the MIT grant covers code only —
> All code is copyrighted by Appditto LLC under the MIT license.
> and "server/assets" folders are copyrighted by Appditto LLC and used by
(BSD-2-Clause, © 1999–2005 Jef Poskanzer; notice retained in the file). With it
